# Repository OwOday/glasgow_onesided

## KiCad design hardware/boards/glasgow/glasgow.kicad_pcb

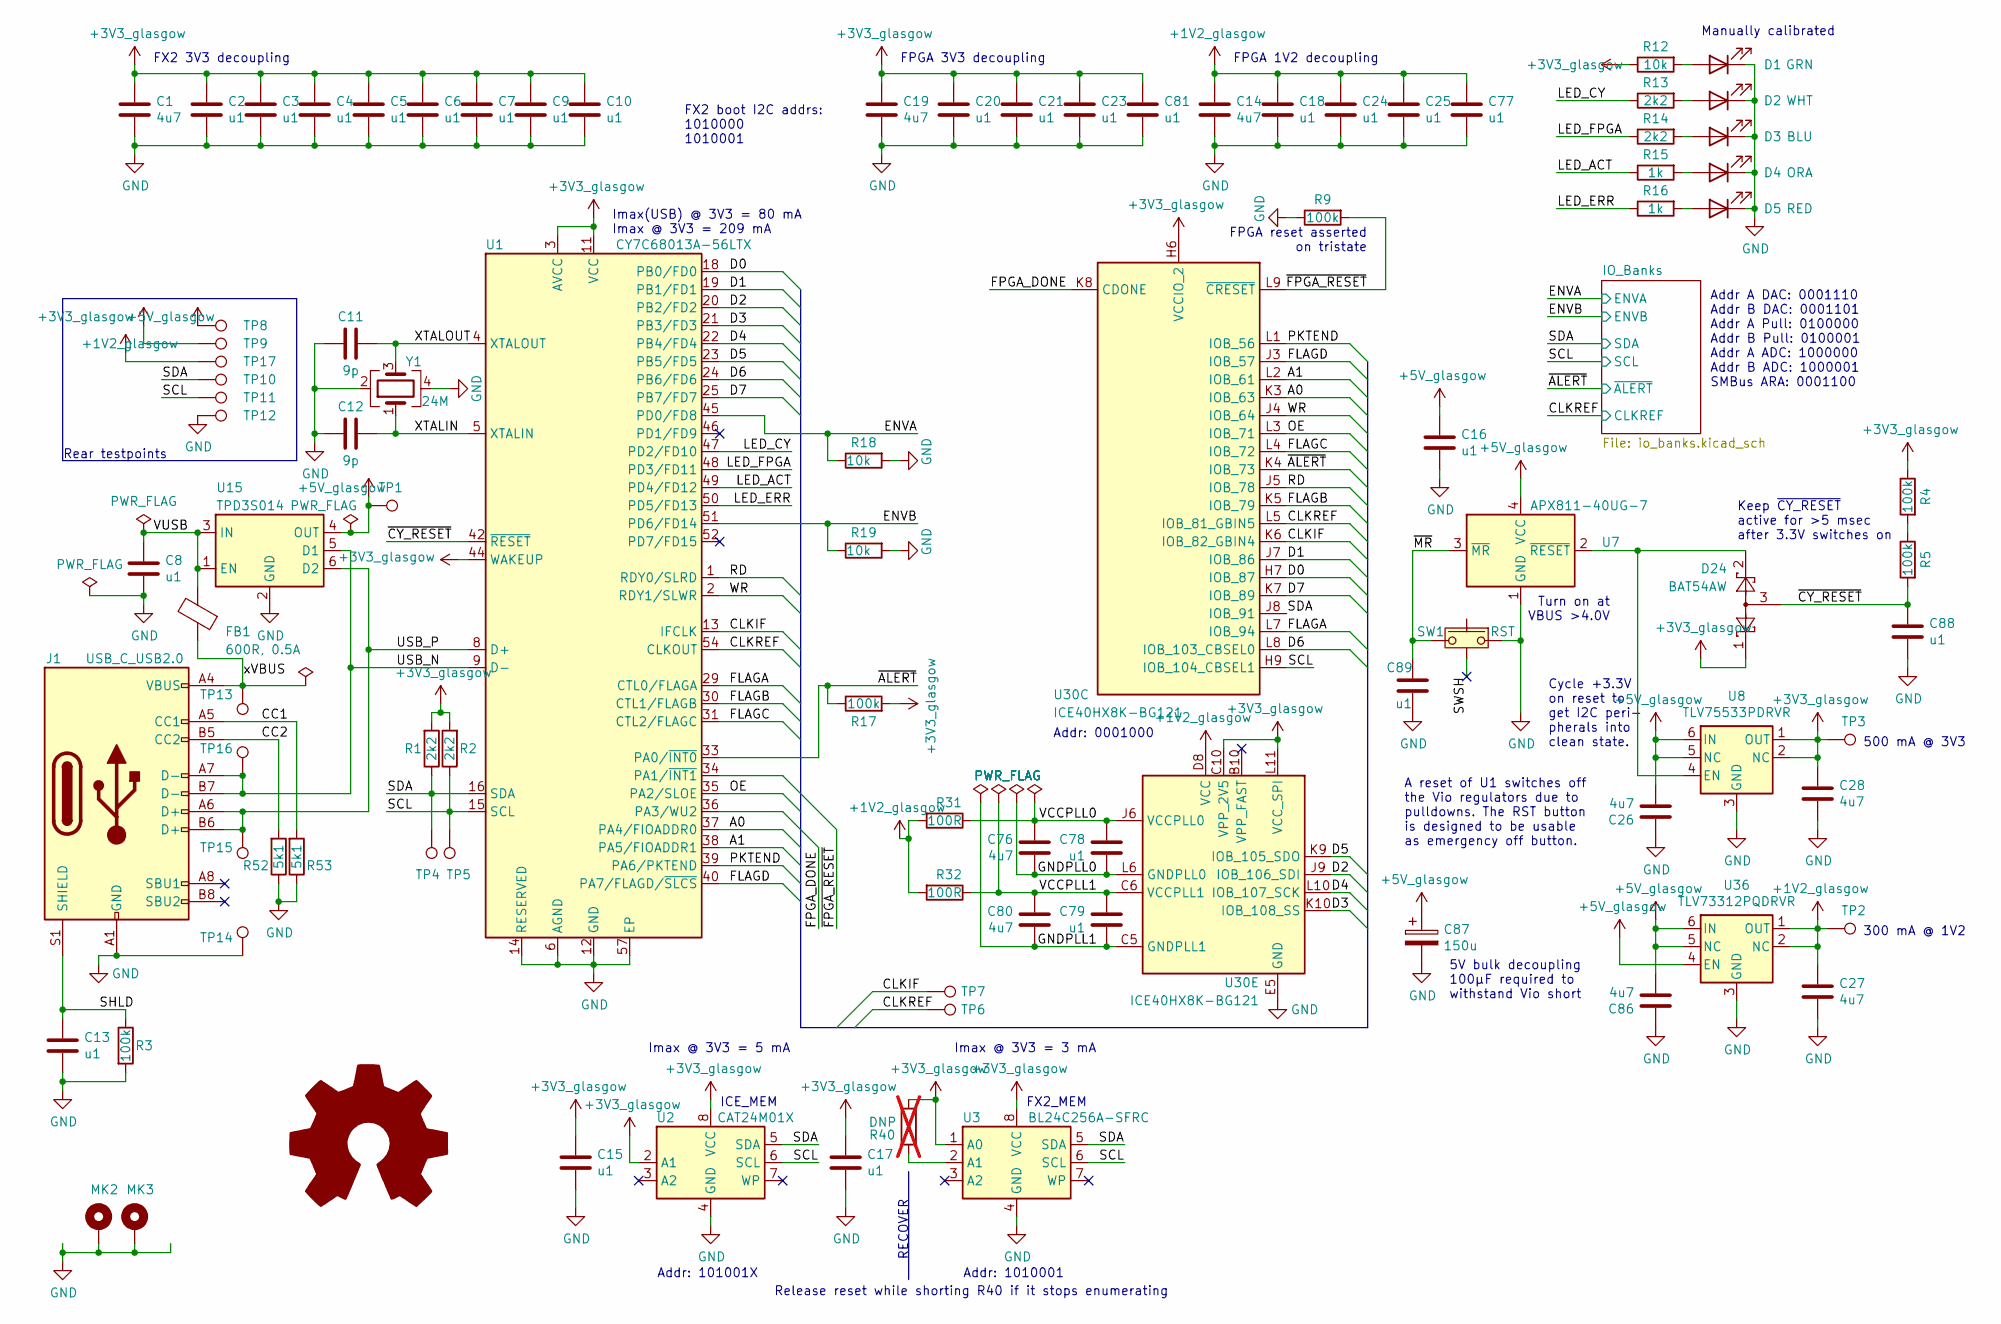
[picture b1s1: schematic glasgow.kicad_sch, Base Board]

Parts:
C1, C14, C19, C26, C27, C28, C76, C80, C86: 4u7; C_0603_1608Metric; MPN LMK107BJ475KAHT
C2, C3, C4, C5, C6, C7, C8, C9, C10, C13, C15, C16, C17, C18, C20, C21, C23, C24, C25, C77, C78, C79, C81, C88, C89: u1; C_0402_1005Metric; MPN TMK105BJ104KV-F
C11, C12: 9p; C_0402_1005Metric; MPN AC0402CRNPO9BN9R0
C87: 150u; CP_Elec_6.3x5.9; MPN A765EB157M1ALAE022
D1: GRN; LED_0603_1608Metric; MPN NCD0603G1
D2: WHT; LED_0603_1608Metric; MPN NCD0603W1
D3: BLU; LED_0603_1608Metric; MPN ORH-B36G
D4: ORA; LED_0603_1608Metric; MPN NCD0603O1
D5: RED; LED_0603_1608Metric; MPN NCD0603R1
D24: BAT54AW; SOT-323_SC-70; MPN BAT54AW-7-F
FB1: 600R, 0.5A; L_0402_1005Metric; MPN BLM15PX601SZ1D
J1: USB_C_USB2.0; USB_C_Receptacle_HRO_TYPE-C-31-M-12; MPN TYPE-C-31-M-12
MK2, MK3: Mounting_Hole_PAD; MountingHole_3.5mm_Pad_Via_CrtYd
R1, R2, R13, R14: 2k2; R_0402_1005Metric; MPN RC0402FR-132K2L
R3, R4, R5, R9, R17: 100k; R_0402_1005Metric; MPN RC0402FR-13100KL
R12, R18, R19: 10k; R_0402_1005Metric; MPN RC0402FR-1310KL
R15, R16: 1k; R_0402_1005Metric
R31, R32: 100R; R_0402_1005Metric; MPN RC0402FR-13100RL
R40: DNP; R_0402_1005Metric_DNP; not fitted
R52, R53: 5k1; R_0402_1005Metric; MPN RC0402FR-075K1L
SW1: RST; SW_Tactile_SPST_Angled_TC-1109DE; MPN TC-1109DE-B-F
TP1, TP8: 5V; TestPoint_Pad_D1.0mm
TP2, TP17: 1V2; TestPoint_Pad_D1.0mm
TP3, TP7, TP9: 3V3; TestPoint_Pad_D1.0mm
TP4, TP10: SDA; TestPoint_Pad_D1.0mm
TP5, TP11: SCL; TestPoint_Pad_D1.0mm
TP6: CLKREF; TestPoint_Pad_D1.0mm
TP12: GND; TestPoint_Pad_D1.0mm
TP13: VBUS; TestPoint_Pad_D1.0mm
TP14: USBGND; TestPoint_Pad_D1.0mm
TP15: USBDP; TestPoint_Pad_D1.0mm
TP16: USBDM; TestPoint_Pad_D1.0mm
U1: CY7C68013A-56LTX; Cypress_QFN-56-1EP_8x8mm_P0.5mm_EP6.22x6.22mm_ThermalVias; MPN CY7C68013A-56LTXC
U2: CAT24M01X; TSSOP-8_4.4x3mm_P0.65mm; MPN CAT24M01YI−GT3
U3: BL24C256A-SFRC; TSSOP-8_4.4x3mm_P0.65mm; MPN BL24C256A-SFRC
U7: APX811-40UG-7; SOT-143; MPN APX811-40UG-7
U8: TLV75533PDRVR; DFN-6-1EP_2x2mm_P0.65mm_EP1x1.6mm_ThermalVias; MPN TLV75533PDRVR
U15: TPD3S014; SOT-23-6; MPN TPD3S014DBVR
U30: ICE40HX8K-BG121; BGA-121_9.0x9.0mm_Layout11x11_P0.8mm_Ball0.4mm_Pad0.35mm_NS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; MPN ICE40HX8K-BG121
U36: TLV73312PQDRVR; DFN-6-1EP_2x2mm_P0.65mm_EP1x1.6mm_ThermalVias; MPN TLV73312PQDRVRQ1
Y1: 24M; Crystal_SMD_3225-4Pin_3.2x2.5mm; MPN JF4024M00009T8188070

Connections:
+1V2_glasgow: C14.1, C18.1, C24.1, C25.1, C27.1, C77.1, R31.2, R32.2, TP2.1, TP17.1, U30.D4 (VCC), U30.D8 (VCC), U30.H4 (VCC), U30.H8 (VCC), U36.1 (OUT), U36.2 (NC)
+3V3_glasgow: C1.1, C2.1, C3.1, C4.1, C5.1, C6.1, C7.1, C9.1, C10.1, C15.1, C17.1, C19.1, C20.1, C21.1, C23.1, C28.1, C81.1, D24.1, R1.2, R2.2, R4.1, R12.1, R17.2, R40.2, TP3.1, TP9.1, U1.3 (AVCC), U1.7 (AVCC), U1.11 (VCC), U1.17 (VCC), U1.27 (VCC), U1.32 (VCC), U1.43 (VCC), U1.44 (WAKEUP), U1.55 (VCC), U2.2 (A1), U2.8 (VCC), U3.1 (A0), U3.8 (VCC), U8.1 (OUT), U8.2 (NC), U30.C10 (VPP_2V5), U30.H6 (VCCIO_2), U30.L11 (VCC_SPI); also elsewhere on the board
+5V_glasgow: C16.1, C26.2, C86.2, C87.1, TP1.1, TP8.1, U7.4 (VCC), U8.5 (NC), U8.6 (IN), U15.4 (OUT), U36.4 (EN), U36.5 (NC), U36.6 (IN); also elsewhere on the board
/A0: U1.37 (PA4/FIOADDR0), U30.K3 (IOB_63)
/A1: U1.38 (PA5/FIOADDR1), U30.L2 (IOB_61)
/CC1: J1.A5 (CC1), R53.2
/CC2: J1.B5 (CC2), R52.2
/CLKIF: TP7.1, U1.13 (IFCLK), U30.K6 (IOB_82_GBIN4)
/CLKREF: TP6.1, U1.54 (CLKOUT), U30.L5 (IOB_81_GBIN5); also elsewhere on the board
/D0: U1.18 (PB0/FD0), U30.H7 (IOB_87)
/D1: U1.19 (PB1/FD1), U30.J7 (IOB_86)
/D2: U1.20 (PB2/FD2), U30.J9 (IOB_106_SDI)
/D3: U1.21 (PB3/FD3), U30.K10 (IOB_108_SS)
/D4: U1.22 (PB4/FD4), U30.L10 (IOB_107_SCK)
/D5: U1.23 (PB5/FD5), U30.K9 (IOB_105_SDO)
/D6: U1.24 (PB6/FD6), U30.L8 (IOB_103_CBSEL0)
/D7: U1.25 (PB7/FD7), U30.K7 (IOB_89)
/ENVA: R18.1, U1.45 (PD0/FD8); also elsewhere on the board
/ENVB: R19.1, U1.51 (PD6/FD14)
/FLAGA: U1.29 (CTL0/FLAGA), U30.L7 (IOB_94)
/FLAGB: U1.30 (CTL1/FLAGB), U30.K5 (IOB_79)
/FLAGC: U1.31 (CTL2/FLAGC), U30.L4 (IOB_72)
/FLAGD: U1.40 (PA7/FLAGD/~SLCS), U30.J3 (IOB_57)
/FPGA_DONE: U1.36 (PA3/WU2), U30.K8 (CDONE)
/GNDPLL0: C76.2, C78.2, U30.L6 (GNDPLL0)
/GNDPLL1: C79.2, C80.2, U30.C5 (GNDPLL1)
/LED_ACT: R15.1, U1.49 (PD4/FD12)
/LED_CY: R13.1, U1.47 (PD2/FD10)
/LED_ERR: R16.1, U1.50 (PD5/FD13)
/LED_FPGA: R14.1, U1.48 (PD3/FD11)
/OE: U1.35 (PA2/SLOE), U30.L3 (IOB_71)
/PKTEND: U1.39 (PA6/PKTEND), U30.L1 (IOB_56)
/RD: U1.1 (RDY0/SLRD), U30.J5 (IOB_78)
/SCL: R2.1, TP5.1, TP11.1, U1.15 (SCL), U2.6 (SCL), U3.6 (SCL), U30.H9 (IOB_104_CBSEL1); also elsewhere on the board
/SDA: R1.1, TP4.1, TP10.1, U1.16 (SDA), U2.5 (SDA), U3.5 (SDA), U30.J8 (IOB_91); also elsewhere on the board
/SHLD: C13.1, J1.S1 (SHIELD), R3.1
/SWSH: SW1.3
/USB_N: J1.A7 (D-), J1.B7 (D-), TP16.1, U1.9 (D-), U15.5 (D1)
/USB_P: J1.A6 (D+), J1.B6 (D+), TP15.1, U1.8 (D+), U15.6 (D2)
/VCCPLL0: C76.1, C78.1, R31.1, U30.J6 (VCCPLL0)
/VCCPLL1: C79.1, C80.1, R32.1, U30.C6 (VCCPLL1)
/VUSB: C8.1, FB1.2, U15.1 (EN), U15.3 (IN)
/WR: U1.2 (RDY1/SLWR), U30.J4 (IOB_64)
/XTALIN: C12.1, U1.5 (XTALIN), Y1.1
/XTALOUT: C11.1, U1.4 (XTALOUT), Y1.3
/xVBUS: FB1.1, J1.A4 (VBUS), J1.A9 (VBUS), J1.B4 (VBUS), J1.B9 (VBUS), TP13.1
/~ALERT: R17.1, U1.33 (PA0/~INT0), U30.K4 (IOB_73); also elsewhere on the board
/~CY_RESET: C88.1, D24.3, R5.2, U1.42 (~RESET)
/~FPGA_RESET: R9.2, U1.34 (PA1/~INT1), U30.L9 (~CRESET)
/~MR: C89.1, SW1.2, U7.3 (~MR)
GND: C1.2, C2.2, C3.2, C4.2, C5.2, C6.2, C7.2, C8.2, C9.2, C10.2, C11.2, C12.2, C13.2, C14.2, C15.2, C16.2, C17.2, C18.2, C19.2, C20.2, C21.2, C23.2, C24.2, C25.2, C26.1, C27.2, C28.2, C77.2, C81.2, C86.1, C87.2, C88.2, C89.2, D1.1 (K), D2.1 (K), D3.1 (K), D4.1 (K), D5.1 (K), J1.A1 (GND), J1.A12 (GND), J1.B1 (GND), J1.B12 (GND), MK2.1, MK3.1, R3.2, R9.1, R18.2, R19.2, R52.1, R53.1, SW1.1, TP12.1, TP14.1, U1.6 (AGND), U1.10 (AGND), U1.12 (GND), U1.14 (RESERVED), U1.26 (GND), U1.28 (GND), U1.41 (GND), U1.53 (GND), U1.56 (GND), U1.57 (EP), U2.4 (GND), U3.4 (GND), U7.1 (GND), U8.3 (GND), U8.7 (GND), U15.2 (GND), U30.E5 (GND), U30.E6 (GND), U30.E7 (GND), U30.F5 (GND), U30.F6 (GND), U30.F7 (GND), U30.G5 (GND), U30.G6 (GND), U30.G7 (GND), U30.H5 (GND), U36.3 (GND), U36.7 (GND), Y1.2, Y1.4; also elsewhere on the board
unnamed: D1.2 (A), R12.2
unnamed: D2.2 (A), R13.2
unnamed: D3.2 (A), R14.2
unnamed: D4.2 (A), R15.2
unnamed: D5.2 (A), R16.2
unnamed: R4.2, R5.1
unnamed: R40.1, U3.2 (A1)
unnamed: D24.2, U7.2 (~RESET), U8.4 (EN)

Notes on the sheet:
Turn on at VBUS >4.0V
Addr: 1010001
RECOVER
Imax @ 3V3 = 3 mA
Cycle +3.3V on reset to get I2C peri- pherals into clean state.
500 mA @ 3V3
FX2_MEM
Release reset while shorting R40 if it stops enumerating
Addr: 0001000
Manually calibrated
FPGA 3V3 decoupling
FPGA reset asserted on tristate
FX2 3V3 decoupling
Imax @ 3V3 = 5 mA
FX2 boot I2C addrs: 1010000 1010001
A reset of U1 switches off the Vio regulators due to pulldowns. The RST button is designed to be usable as emergency off button.
Addr A DAC: 0001110 Addr B DAC: 0001101 Addr A Pull: 0100000 Addr B Pull: 0100001 Addr A ADC: 1000000 Addr B ADC: 1000001 SMBus ARA: 0001100
Rear testpoints
5V bulk decoupling 100µF required to withstand Vio short
Imax(USB) @ 3V3 = 80 mA Imax @ 3V3 = 209 mA
FPGA 1V2 decoupling
Addr: 101001X
Keep ~{CY_RESET} active for >5 msec after 3.3V switches on
300 mA @ 1V2
ICE_MEM

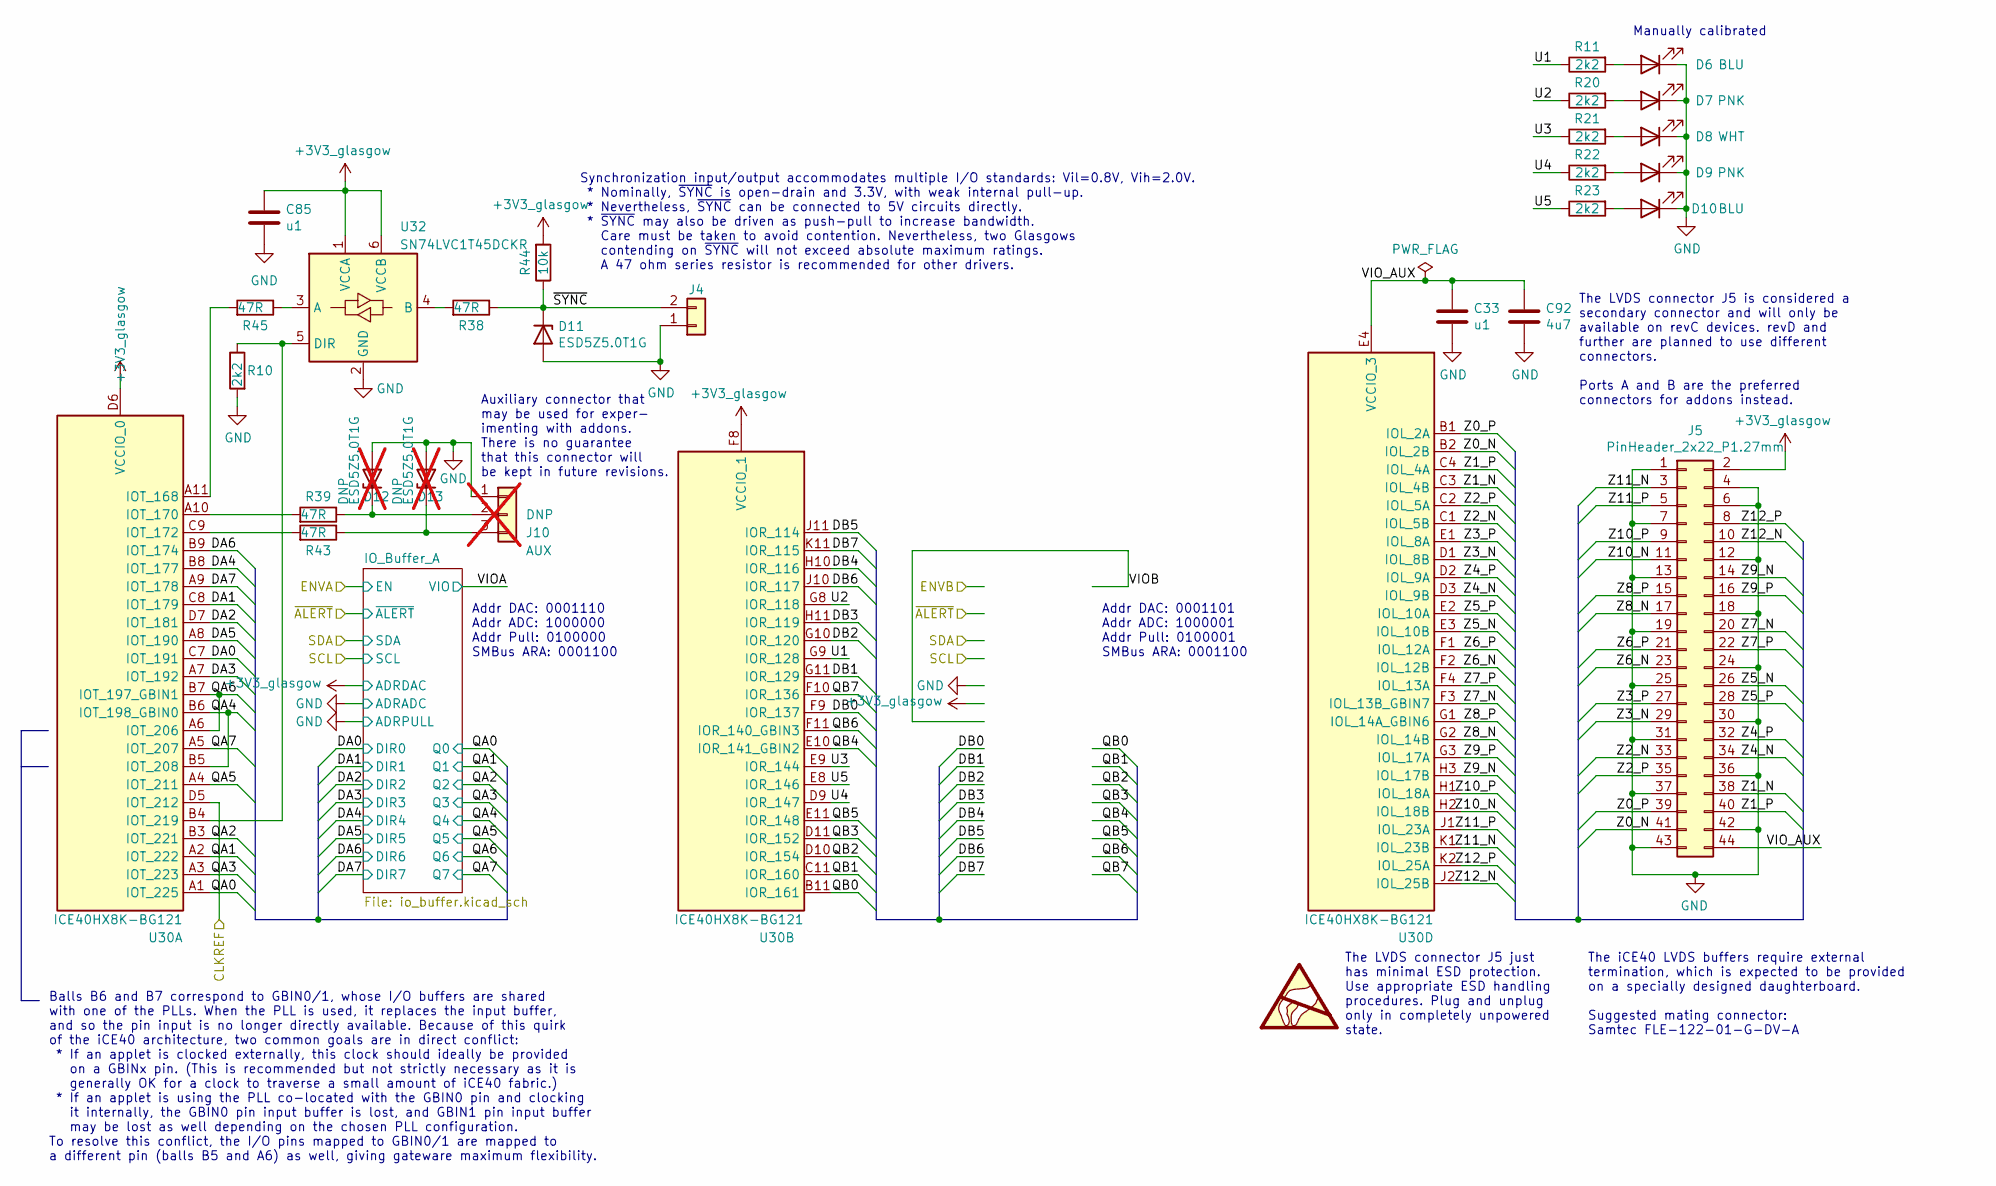
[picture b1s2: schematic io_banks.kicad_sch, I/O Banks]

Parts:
C33, C85: u1; C_0402_1005Metric; MPN TMK105BJ104KV-F
C92: 4u7; C_0603_1608Metric; MPN LMK107BJ475KAHT
D6, D10: BLU; LED_0603_1608Metric; MPN ORH-B36G
D7, D9: PNK; LED_0603_1608Metric; MPN OSK40603C1E
D8: WHT; LED_0603_1608Metric; MPN NCD0603W1
D11: ESD5Z5.0T1G; D_SOD-523; MPN ESD5Z5.0T1G
D12, D13: ESD5Z5.0T1G; D_SOD-523; MPN ESD5Z5.0T1G; not fitted
J4: Conn_01x02; Molex_KK-254_1x02_P2.54mm_Horizontal; MPN 22-05-3021
J5: PinHeader_2x22_P1.27mm; PinHeader_2x22_P1.27mm_Vertical__SMD; MPN FTS-122-01-L-DV
J10: AUX; PinHeader_1x03_P2.54mm_Vertical; not fitted
R10, R11, R20, R21, R22, R23: 2k2; R_0402_1005Metric; MPN RC0402FR-132K2L
R38, R39, R43, R45: 47R; R_0402_1005Metric; MPN RC0402FR-1347RL
R44: 10k; R_0402_1005Metric; MPN RC0402FR-1310KL
U30: ICE40HX8K-BG121; BGA-121_9.0x9.0mm_Layout11x11_P0.8mm_Ball0.4mm_Pad0.35mm_NS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; MPN ICE40HX8K-BG121
U32: SN74LVC1T45DCKR; SOT-363_SC-70-6; MPN SN74LVC1T45DCKR

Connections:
+3V3_glasgow: C85.1, J5.2, R44.2, U30.D6 (VCCIO_0), U30.F8 (VCCIO_1), U32.1 (VCCA), U32.6 (VCCB); also elsewhere on the board
/CLKREF: U30.D5 (IOT_212); also elsewhere on the board
/IO_Banks/DA0: U30.C7 (IOT_191); also elsewhere on the board
/IO_Banks/DA1: U30.C8 (IOT_179); also elsewhere on the board
/IO_Banks/DA2: U30.D7 (IOT_181); also elsewhere on the board
/IO_Banks/DA3: U30.A7 (IOT_192); also elsewhere on the board
/IO_Banks/DA4: U30.B8 (IOT_177); also elsewhere on the board
/IO_Banks/DA5: U30.A8 (IOT_190); also elsewhere on the board
/IO_Banks/DA6: U30.B9 (IOT_174); also elsewhere on the board
/IO_Banks/DA7: U30.A9 (IOT_178); also elsewhere on the board
/IO_Banks/DB0: U30.F9 (IOR_137)
/IO_Banks/DB1: U30.G11 (IOR_129)
/IO_Banks/DB2: U30.G10 (IOR_120)
/IO_Banks/DB3: U30.H11 (IOR_119)
/IO_Banks/DB4: U30.H10 (IOR_116)
/IO_Banks/DB5: U30.J11 (IOR_114)
/IO_Banks/DB6: U30.J10 (IOR_117)
/IO_Banks/DB7: U30.K11 (IOR_115)
/IO_Banks/QA0: U30.A1 (IOT_225); also elsewhere on the board
/IO_Banks/QA1: U30.A2 (IOT_222); also elsewhere on the board
/IO_Banks/QA2: U30.B3 (IOT_221); also elsewhere on the board
/IO_Banks/QA3: U30.A3 (IOT_223); also elsewhere on the board
/IO_Banks/QA4: U30.B5 (IOT_208), U30.B6 (IOT_198_GBIN0); also elsewhere on the board
/IO_Banks/QA5: U30.A4 (IOT_211); also elsewhere on the board
/IO_Banks/QA6: U30.A6 (IOT_206), U30.B7 (IOT_197_GBIN1); also elsewhere on the board
/IO_Banks/QA7: U30.A5 (IOT_207); also elsewhere on the board
/IO_Banks/QB0: U30.B11 (IOR_161)
/IO_Banks/QB1: U30.C11 (IOR_160)
/IO_Banks/QB2: U30.D10 (IOR_154)
/IO_Banks/QB3: U30.D11 (IOR_152)
/IO_Banks/QB4: U30.E10 (IOR_141_GBIN2)
/IO_Banks/QB5: U30.E11 (IOR_148)
/IO_Banks/QB6: U30.F11 (IOR_140_GBIN3)
/IO_Banks/QB7: U30.F10 (IOR_136)
/IO_Banks/U1: R11.1, U30.G9 (IOR_128)
/IO_Banks/U2: R20.1, U30.G8 (IOR_118)
/IO_Banks/U3: R21.1, U30.E9 (IOR_144)
/IO_Banks/U4: R22.1, U30.D9 (IOR_147)
/IO_Banks/U5: R23.1, U30.E8 (IOR_146)
/IO_Banks/VIO_AUX: C33.1, C92.1, J5.44, U30.E4 (VCCIO_3), U30.G4 (VCCIO_3)
/IO_Banks/Z0_N: J5.41, U30.B2 (IOL_2B)
/IO_Banks/Z0_P: J5.39, U30.B1 (IOL_2A)
/IO_Banks/Z1_N: J5.38, U30.C3 (IOL_4B)
/IO_Banks/Z1_P: J5.40, U30.C4 (IOL_4A)
/IO_Banks/Z2_N: J5.33, U30.C1 (IOL_5B)
/IO_Banks/Z2_P: J5.35, U30.C2 (IOL_5A)
/IO_Banks/Z3_N: J5.29, U30.D1 (IOL_8B)
/IO_Banks/Z3_P: J5.27, U30.E1 (IOL_8A)
/IO_Banks/Z4_N: J5.34, U30.D3 (IOL_9B)
/IO_Banks/Z4_P: J5.32, U30.D2 (IOL_9A)
/IO_Banks/Z5_N: J5.26, U30.E3 (IOL_10B)
/IO_Banks/Z5_P: J5.28, U30.E2 (IOL_10A)
/IO_Banks/Z6_N: J5.23, U30.F2 (IOL_12B)
/IO_Banks/Z6_P: J5.21, U30.F1 (IOL_12A)
/IO_Banks/Z7_N: J5.20, U30.F3 (IOL_13B_GBIN7)
/IO_Banks/Z7_P: J5.22, U30.F4 (IOL_13A)
/IO_Banks/Z8_N: J5.17, U30.G2 (IOL_14B)
/IO_Banks/Z8_P: J5.15, U30.G1 (IOL_14A_GBIN6)
/IO_Banks/Z9_N: J5.14, U30.H3 (IOL_17B)
/IO_Banks/Z9_P: J5.16, U30.G3 (IOL_17A)
/IO_Banks/Z10_N: J5.11, U30.H2 (IOL_18B)
/IO_Banks/Z10_P: J5.9, U30.H1 (IOL_18A)
/IO_Banks/Z11_N: J5.3, U30.K1 (IOL_23B)
/IO_Banks/Z11_P: J5.5, U30.J1 (IOL_23A)
/IO_Banks/Z12_N: J5.10, U30.J2 (IOL_25B)
/IO_Banks/Z12_P: J5.8, U30.K2 (IOL_25A)
/IO_Banks/~SYNC: D11.1 (K), J4.2, R38.1, R44.1
GND: C33.2, C85.2, C92.2, D6.1 (K), D7.1 (K), D8.1 (K), D9.1 (K), D10.1 (K), D11.2 (A), D12.2 (A), D13.2 (A), J4.1, J5.1, J5.4, J5.6, J5.7, J5.12, J5.13, J5.18, J5.19, J5.24, J5.25, J5.30, J5.31, J5.36, J5.37, J5.42, J5.43, J10.1, R10.2, U32.2 (GND); also elsewhere on the board
unnamed: D6.2 (A), R11.2
unnamed: D7.2 (A), R20.2
unnamed: D8.2 (A), R21.2
unnamed: D9.2 (A), R22.2
unnamed: D10.2 (A), R23.2
unnamed: D12.1 (K), J10.2, R39.1
unnamed: D13.1 (K), J10.3, R43.1
unnamed: R45.2, U30.A11 (IOT_168)
unnamed: R39.2, U30.A10 (IOT_170)
unnamed: R43.2, U30.C9 (IOT_172)
unnamed: R10.1, U30.B4 (IOT_219), U32.5 (DIR)
unnamed: R45.1, U32.3 (A)
unnamed: R38.2, U32.4 (B)

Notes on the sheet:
The LVDS connector J5 is considered a secondary connector and will only be available on revC devices. revD and further are planned to use different connectors. Ports A and B are the preferred connectors for addons instead.
Addr DAC: 0001101 Addr ADC: 1000001 Addr Pull: 0100001 SMBus ARA: 0001100
The iCE40 LVDS buffers require external termination, which is expected to be provided on a specially designed daughterboard. Suggested mating connector: Samtec FLE-122-01-G-DV-A
Auxiliary connector that may be used for exper- imenting with addons. There is no guarantee that this connector will be kept in future revisions.
Manually calibrated
Addr DAC: 0001110 Addr ADC: 1000000 Addr Pull: 0100000 SMBus ARA: 0001100
Balls B6 and B7 correspond to GBIN0/1, whose I/O buffers are shared with one of the PLLs. When the PLL is used, it replaces the input buffer, and so the pin input is no longer directly available. Because of this quirk of the iCE40 architecture, two common goals are in direct conflict: * If an apple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
Synchronization input/output accommodates multiple I/O standards: Vil=0.8V, Vih=2.0V. * Nominally, ~{SYNC} is open-drain and 3.3V, with weak internal pull-up. * Nevertheless, ~{SYNC} can be connected to 5V circuits directly. * ~{SYNC} may also be driven as push-pull to increase bandwidth. Care must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
The LVDS connector J5 just has minimal ESD protection. Use appropriate ESD handling procedures. Plug and unplug only in completely unpowered state.

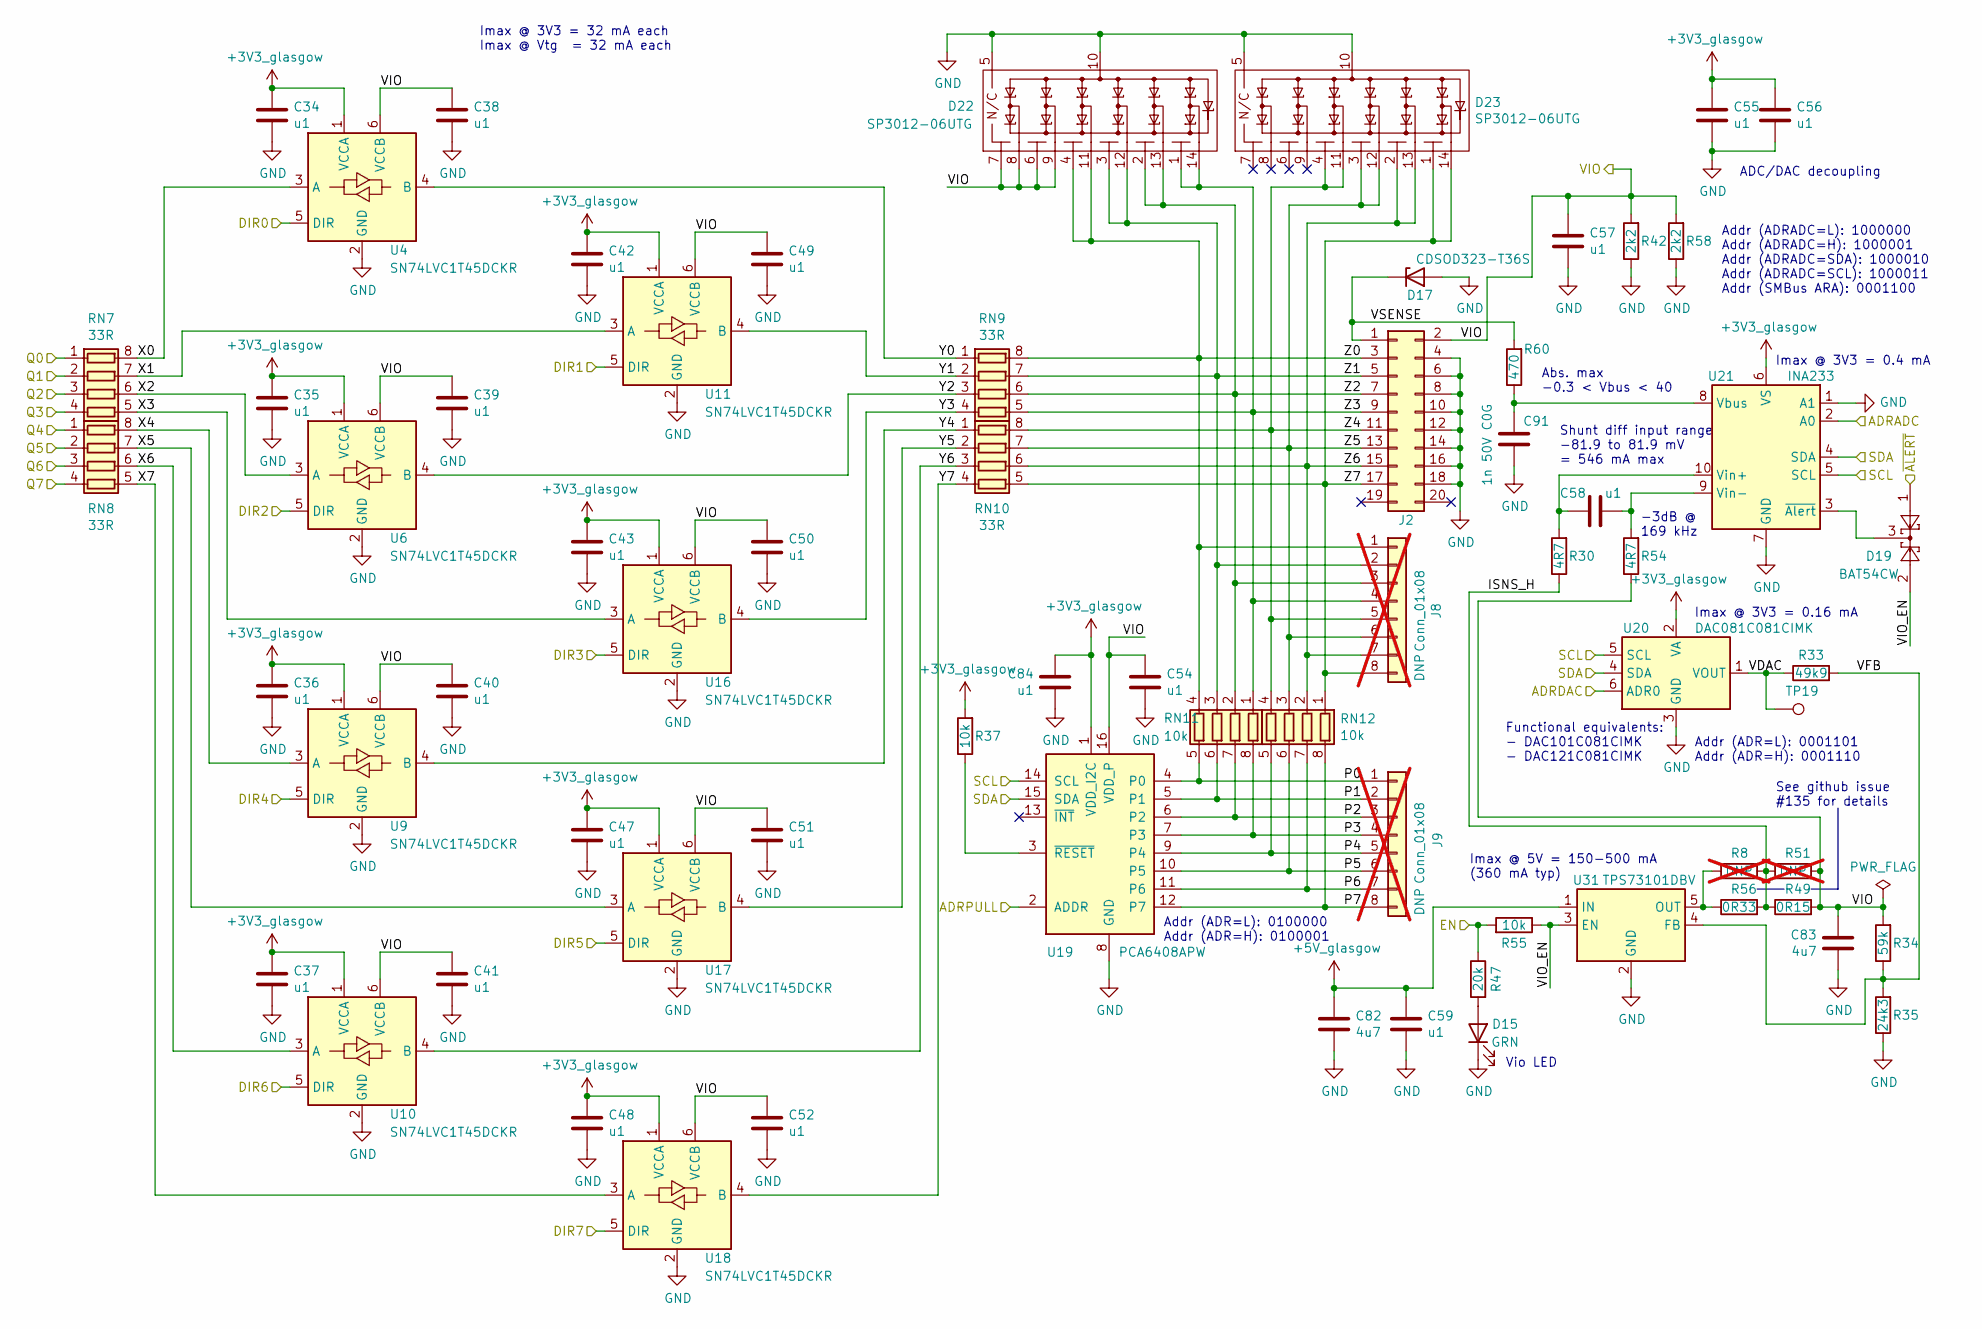
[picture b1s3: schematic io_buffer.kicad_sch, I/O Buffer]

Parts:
C34, C35, C36, C37, C38, C39, C40, C41, C42, C43, C47, C48, C49, C50, C51, C52, C54, C55, C56, C57, C58, C59, C84: u1; C_0402_1005Metric; MPN TMK105BJ104KV-F
C82, C83: 4u7; C_0603_1608Metric; MPN LMK107BJ475KAHT
C91: 1n 50V C0G; C_0402_1005Metric; MPN GCM1555C1H102JA16J
D15: GRN; LED_0603_1608Metric; MPN NCD0603G1
D17: CDSOD323-T36S; D_SOD-323; MPN CDSOD323-T36S
D19: BAT54CW; SOT-323_SC-70; MPN BAT54CW-7-F
D22, D23: SP3012-06UTG; UDFN-14_3.5x1.35mm_P0.5mm; MPN SP3012-06UTG
J2: IDC-Header_2x10_P2.54mm; IDC-Header_2x10_P2.54mm_Vertical; MPN 87834-2019
J8, J9: Conn_01x08; PinSocket_1x08_P1.27mm_Vertical_DNP; not fitted
R8, R51: DNP; R_0603_1608Metric_DNP; not fitted
R30, R54: 4R7; R_0402_1005Metric; MPN RC0402FR-074R7L
R33: 49k9; R_0402_1005Metric; MPN RC0402FR-1349K9L
R34: 59k; R_0402_1005Metric; MPN RC0402FR-1359KL
R35: 24k3; R_0402_1005Metric; MPN RC0402FR-1324K3L
R37, R55: 10k; R_0402_1005Metric; MPN RC0402FR-1310KL
R42, R58: 2k2; R_0402_1005Metric; MPN RC0402FR-132K2L
R47: 20k; R_0402_1005Metric; MPN RC0402FR-1320KL
R49: 0R15; R_0603_1608Metric; MPN KDV06FR150ET
R56: 0R33; R_0603_1608Metric; MPN KDV06FR330ET
R60: 470; R_0402_1005Metric; MPN RC0402FR-07470RL
RN7, RN8, RN9, RN10: 33R; R_Array_Convex_4x0402; MPN YC124-JR-1333RL
RN11, RN12: 10k; R_Array_Convex_4x0402; MPN YC124-JR-0710KL
TP19: VDAC; TestPoint_Pad_D1.0mm
U4, U6, U9, U10, U11, U16, U17, U18: SN74LVC1T45DCKR; SOT-363_SC-70-6; MPN SN74LVC1T45DCKR
U19: PCA6408APW; TSSOP-16_4.4x5mm_P0.65mm; MPN PCA6408APW
U20: DAC081C081CIMK; SOT-23-6; MPN DAC081C081CIMK/NOPB
U21: INA233; VSSOP-10_3x3mm_P0.5mm; MPN INA233AIDGSR
U31: TPS73101DBV; SOT-23-5; MPN TPS73101DBVR

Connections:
+3V3_glasgow: C34.1, C35.1, C36.1, C37.1, C42.1, C43.1, C47.1, C48.1, C55.1, C56.1, C84.1, R37.2, U4.1 (VCCA), U6.1 (VCCA), U9.1 (VCCA), U10.1 (VCCA), U11.1 (VCCA), U16.1 (VCCA), U17.1 (VCCA), U18.1 (VCCA), U19.1 (VDD_I2C), U20.2 (VA), U20.6 (ADR0), U21.6 (VS); also elsewhere on the board
+5V_glasgow: C59.1, C82.1, U31.1 (IN); also elsewhere on the board
/ENVA: R47.1, R55.2; also elsewhere on the board
/IO_Banks/DA0: U4.5 (DIR); also elsewhere on the board
/IO_Banks/DA1: U11.5 (DIR); also elsewhere on the board
/IO_Banks/DA2: U6.5 (DIR); also elsewhere on the board
/IO_Banks/DA3: U16.5 (DIR); also elsewhere on the board
/IO_Banks/DA4: U9.5 (DIR); also elsewhere on the board
/IO_Banks/DA5: U17.5 (DIR); also elsewhere on the board
/IO_Banks/DA6: U10.5 (DIR); also elsewhere on the board
/IO_Banks/DA7: U18.5 (DIR); also elsewhere on the board
/IO_Banks/IO_Buffer_A/ISNS_H: R8.2, R30.1, R49.1, R51.1, R56.2
/IO_Banks/IO_Buffer_A/P0: J9.1, RN11.5 (R4.2), U19.4 (P0)
/IO_Banks/IO_Buffer_A/P1: J9.2, RN11.6 (R3.2), U19.5 (P1)
/IO_Banks/IO_Buffer_A/P2: J9.3, RN11.7 (R2.2), U19.6 (P2)
/IO_Banks/IO_Buffer_A/P3: J9.4, RN11.8 (R1.2), U19.7 (P3)
/IO_Banks/IO_Buffer_A/P4: J9.5, RN12.5 (R4.2), U19.9 (P4)
/IO_Banks/IO_Buffer_A/P5: J9.6, RN12.6 (R3.2), U19.10 (P5)
/IO_Banks/IO_Buffer_A/P6: J9.7, RN12.7 (R2.2), U19.11 (P6)
/IO_Banks/IO_Buffer_A/P7: J9.8, RN12.8 (R1.2), U19.12 (P7)
/IO_Banks/IO_Buffer_A/VDAC: R33.1, TP19.1, U20.1 (VOUT)
/IO_Banks/IO_Buffer_A/VFB: R33.2, R34.1, R35.2, U31.4 (FB)
/IO_Banks/IO_Buffer_A/VIO_EN: D19.2, R55.1, U31.3 (EN)
/IO_Banks/IO_Buffer_A/VSENSE: D17.1 (K), J2.1, R60.2
/IO_Banks/IO_Buffer_A/X0: RN7.8 (R1.2), U4.3 (A)
/IO_Banks/IO_Buffer_A/X1: RN7.7 (R2.2), U11.3 (A)
/IO_Banks/IO_Buffer_A/X2: RN7.6 (R3.2), U6.3 (A)
/IO_Banks/IO_Buffer_A/X3: RN7.5 (R4.2), U16.3 (A)
/IO_Banks/IO_Buffer_A/X4: RN8.8 (R1.2), U9.3 (A)
/IO_Banks/IO_Buffer_A/X5: RN8.7 (R2.2), U17.3 (A)
/IO_Banks/IO_Buffer_A/X6: RN8.6 (R3.2), U10.3 (A)
/IO_Banks/IO_Buffer_A/X7: RN8.5 (R4.2), U18.3 (A)
/IO_Banks/IO_Buffer_A/Y0: RN9.1 (R1.1), U4.4 (B)
/IO_Banks/IO_Buffer_A/Y1: RN9.2 (R2.1), U11.4 (B)
/IO_Banks/IO_Buffer_A/Y2: RN9.3 (R3.1), U6.4 (B)
/IO_Banks/IO_Buffer_A/Y3: RN9.4 (R4.1), U16.4 (B)
/IO_Banks/IO_Buffer_A/Y4: RN10.1 (R1.1), U9.4 (B)
/IO_Banks/IO_Buffer_A/Y5: RN10.2 (R2.1), U17.4 (B)
/IO_Banks/IO_Buffer_A/Y6: RN10.3 (R3.1), U10.4 (B)
/IO_Banks/IO_Buffer_A/Y7: RN10.4 (R4.1), U18.4 (B)
/IO_Banks/IO_Buffer_A/Z0: D22.4 (N/C), D22.11 (Ch4), J2.3, J8.1, RN9.8 (R1.2), RN11.4 (R4.1)
/IO_Banks/IO_Buffer_A/Z1: D22.3 (N/C), D22.12 (Ch3), J2.5, J8.2, RN9.7 (R2.2), RN11.3 (R3.1)
/IO_Banks/IO_Buffer_A/Z2: D22.2 (N/C), D22.13 (Ch2), J2.7, J8.3, RN9.6 (R3.2), RN11.2 (R2.1)
/IO_Banks/IO_Buffer_A/Z3: D22.1 (N/C), D22.14 (Ch1), J2.9, J8.4, RN9.5 (R4.2), RN11.1 (R1.1)
/IO_Banks/IO_Buffer_A/Z4: D23.4 (N/C), D23.11 (Ch4), J2.11, J8.5, RN10.8 (R1.2), RN12.4 (R4.1)
/IO_Banks/IO_Buffer_A/Z5: D23.3 (N/C), D23.12 (Ch3), J2.13, J8.6, RN10.7 (R2.2), RN12.3 (R3.1)
/IO_Banks/IO_Buffer_A/Z6: D23.2 (N/C), D23.13 (Ch2), J2.15, J8.7, RN10.6 (R3.2), RN12.2 (R2.1)
/IO_Banks/IO_Buffer_A/Z7: D23.1 (N/C), D23.14 (Ch1), J2.17, J8.8, RN10.5 (R4.2), RN12.1 (R1.1)
/IO_Banks/QA0: RN7.1 (R1.1); also elsewhere on the board
/IO_Banks/QA1: RN7.2 (R2.1); also elsewhere on the board
/IO_Banks/QA2: RN7.3 (R3.1); also elsewhere on the board
/IO_Banks/QA3: RN7.4 (R4.1); also elsewhere on the board
/IO_Banks/QA4: RN8.1 (R1.1); also elsewhere on the board
/IO_Banks/QA5: RN8.2 (R2.1); also elsewhere on the board
/IO_Banks/QA6: RN8.3 (R3.1); also elsewhere on the board
/IO_Banks/QA7: RN8.4 (R4.1); also elsewhere on the board
/IO_Banks/VIOA: C38.1, C39.1, C40.1, C41.1, C49.1, C50.1, C51.1, C52.1, C54.1, C57.1, C83.1, D22.6 (N/C), D22.7 (N/C), D22.8 (Ch6), D22.9 (Ch5), J2.2, R34.2, R42.2, R49.2, R51.2, R54.1, R58.2, U4.6 (VCCB), U6.6 (VCCB), U9.6 (VCCB), U10.6 (VCCB), U11.6 (VCCB), U16.6 (VCCB), U17.6 (VCCB), U18.6 (VCCB), U19.16 (VDD_P)
/SCL: U19.14 (SCL), U20.5 (SCL), U21.5 (SCL); also elsewhere on the board
/SDA: U19.15 (SDA), U20.4 (SDA), U21.4 (SDA); also elsewhere on the board
/~ALERT: D19.1; also elsewhere on the board
GND: C34.2, C35.2, C36.2, C37.2, C38.2, C39.2, C40.2, C41.2, C42.2, C43.2, C47.2, C48.2, C49.2, C50.2, C51.2, C52.2, C54.2, C55.2, C56.2, C57.2, C59.2, C82.2, C83.2, C84.2, C91.1, D15.1 (K), D17.2 (A), D22.5 (N/C), D22.10 (GND), D23.5 (N/C), D23.10 (GND), J2.4, J2.6, J2.8, J2.10, J2.12, J2.14, J2.16, J2.18, R35.1, R42.1, R58.1, U4.2 (GND), U6.2 (GND), U9.2 (GND), U10.2 (GND), U11.2 (GND), U16.2 (GND), U17.2 (GND), U18.2 (GND), U19.2 (ADDR), U19.8 (GND), U20.3 (GND), U21.1 (A1), U21.2 (A0), U21.7 (GND), U31.2 (GND); also elsewhere on the board
unnamed: D15.2 (A), R47.2
unnamed: R37.1, U19.3 (~RESET)
unnamed: C91.2, R60.1, U21.8 (Vbus)
unnamed: C58.2, R30.2, U21.10 (Vin+)
unnamed: C58.1, R54.2, U21.9 (Vin-)
unnamed: D19.3, U21.3 (~Alert)
unnamed: R8.1, R56.1, U31.5 (OUT)

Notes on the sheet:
Imax @ 5V = 150-500 mA (360 mA typ)
ADC/DAC decoupling
Vio LED
Imax @ 3V3 = 32 mA each Imax @ Vtg = 32 mA each
Imax @ 3V3 = 0.4 mA
Shunt diff input range -81.9 to 81.9 mV = 546 mA max
See github issue #135 for details
Abs. max -0.3 < Vbus < 40
-3dB @ 169 kHz
Addr (ADR=L): 0001101 Addr (ADR=H): 0001110
Addr (ADR=L): 0100000 Addr (ADR=H): 0100001
Addr (ADRADC=L): 1000000 Addr (ADRADC=H): 1000001 Addr (ADRADC=SDA): 1000010 Addr (ADRADC=SCL): 1000011 Addr (SMBus ARA): 0001100
Functional equivalents: - DAC101C081CIMK - DAC121C081CIMK
Imax @ 3V3 = 0.16 mA

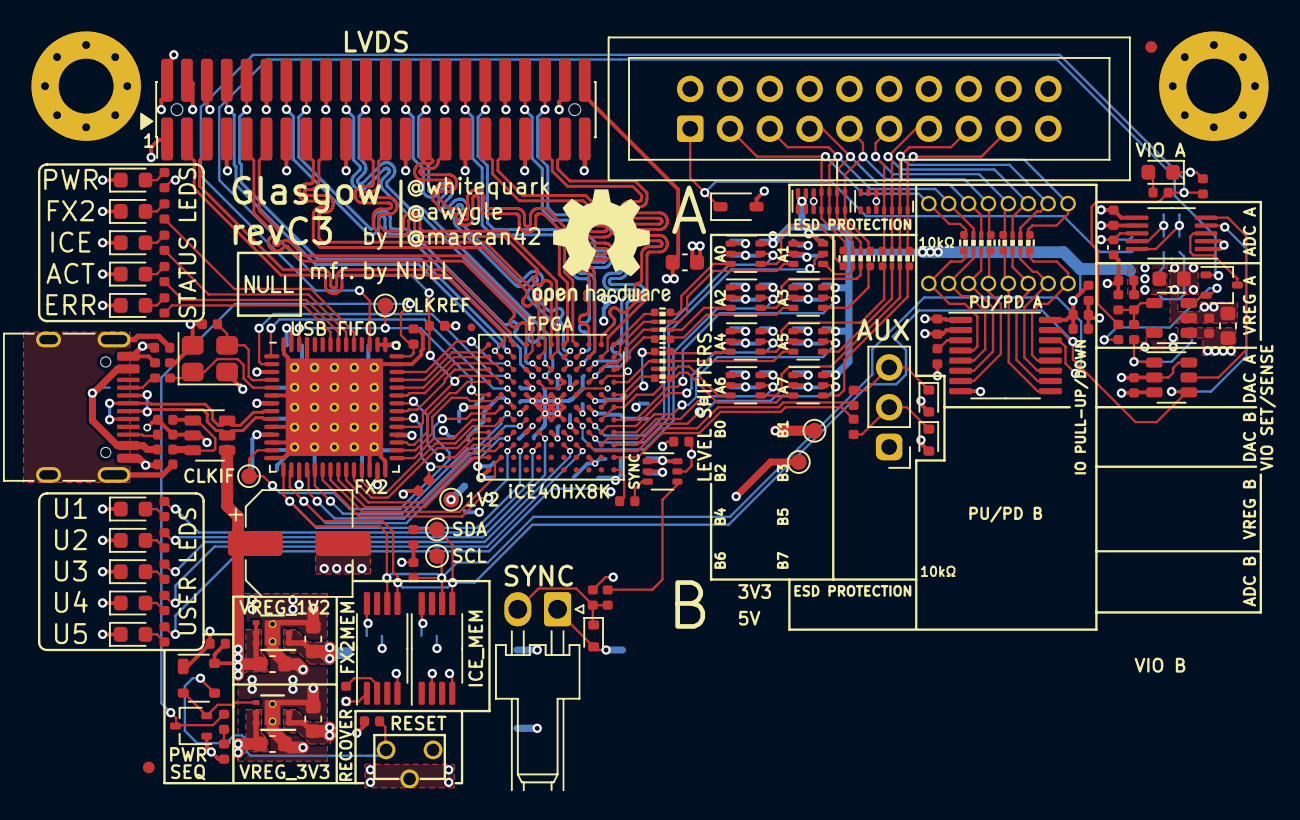
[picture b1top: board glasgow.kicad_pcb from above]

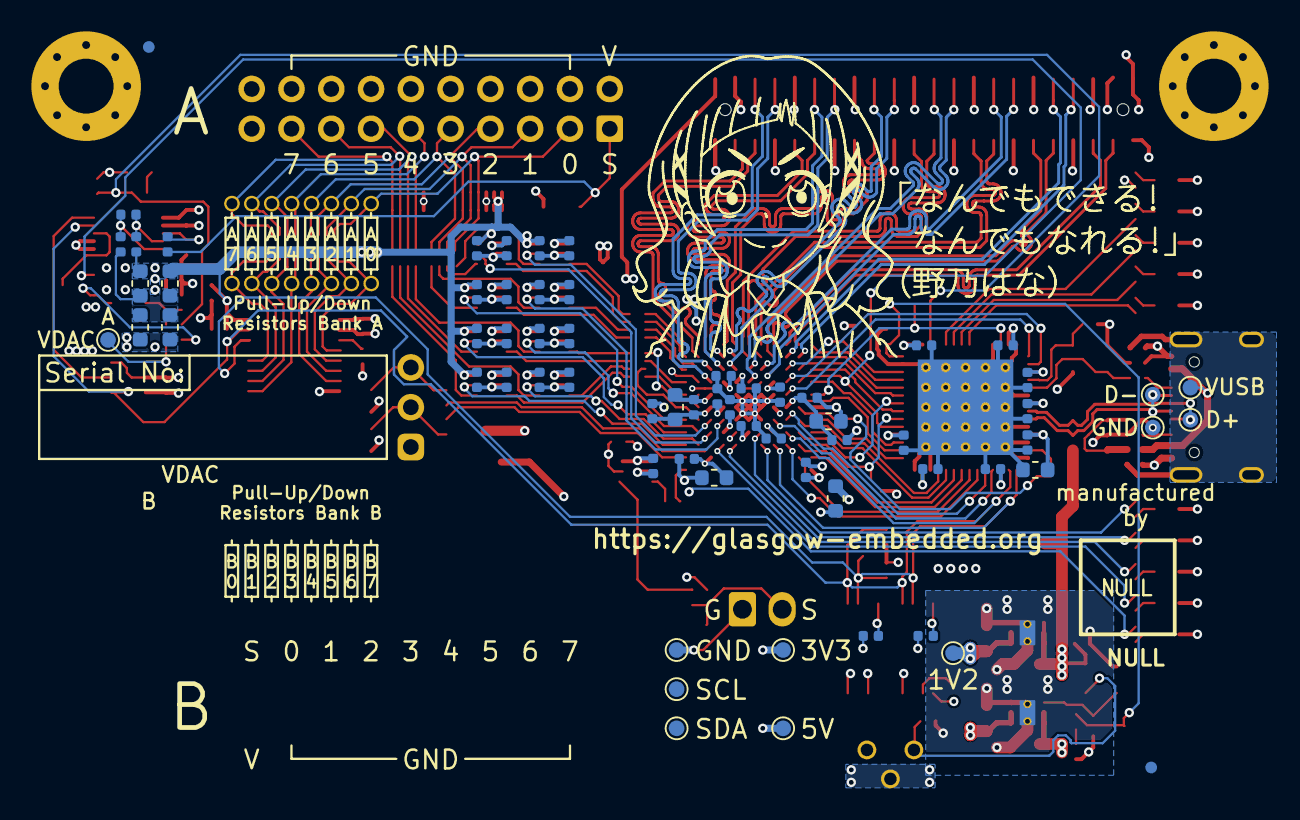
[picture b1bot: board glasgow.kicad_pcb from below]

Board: 4 copper layers, 192 parts (67 on the bottom side), 164 nets.

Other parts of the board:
FID1, FID2, FID4, FID5: Fiducial_0.75mm_Mask1.5mm
FID8: Fiducial_0.5mm_Dia_1mm_Outer
NONO_HANA: MECHOKKU; nono_hana_lines

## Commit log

2026-03-15 Remove one of the sides
